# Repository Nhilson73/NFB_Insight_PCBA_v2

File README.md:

# NFB Insight PCBA v2

PCBA **shield/carrier** para **Nebula Fermentation Insight®**, diseñada alrededor del factor de forma inmutable del **Arduino UNO Q**. El repositorio `Nhilson73/nebula_qshield_pcb` es únicamente donante de ingeniería/trazabilidad; no gobierna placement, routing ni topología de producción V2.

## Fuente primaria UNO Q

Toda decisión dependiente del Arduino UNO Q se contrasta primero contra repositorios oficiales Arduino en GitHub (`github.com/Arduino`, especialmente `arduino/docs-content`), luego `docs.arduino.cc` y finalmente datasheets oficiales. La jerarquía y snapshots revisados viven en `docs/SOURCE_OF_TRUTH.md`.

## Frontera del producto / compliance

NFB Insight PCBA v2 es un **shield/carrier del UNO Q**, no un rediseño de su radio. No añade transmisores, antena, matching ni amplificación RF. El **EU Compliance Design Gate** vive en `docs/EU_COMPLIANCE_GATE.md` / `compliance/eu_compliance_contract.json` y cubre EMC, RoHS 3, REACH, WEEE, RED/CE del producto integrado.

## Mecánica y placement — PR #16 / #17 / ECO PR #22 / #24

- UNO Q rotado; origen global `(0,0)`; USB-C hacia `-Y`.
- Envolvente UNO Q / Z0: `53.34 × 68.58 mm`.
- Altura total PCB fija `68.58 mm`; crecimiento solo `+X`.
- `Y=0` = FIELD I/O EDGE; cables hacia `-Y`.
- Gradiente: Z0 UNO Q → Z1 sensores → Z2 digital → Z3 potencia → Z4 actuadores.
- **Ancho final de placement: `242.34 mm`.**
- Z0 `0.00→53.34 mm`.
- Z1 `53.34→108.84 mm` = `55.50 mm`.
- Z2 `108.84→163.34 mm` = `54.50 mm`.
- Z3 `163.34→198.34 mm` = `35.00 mm`.
- Z4 `198.34→242.34 mm` = `44.00 mm`.
- 119 footprints de producción + `J_UNOQ` = 120 footprints.
- 60 nets materializadas desde PR19D; `5V_HMI` es la net ECO añadida después de PR19C.
- PR17 cerró courtyard overlaps y fallos físicos de placement.
- PR22 aplicó el ECO acotado de placement alrededor del `TPSM33625` en Z3.
- PR24 acercó `TP_LOAD_A_POS/NEG` al HX711 en Z2 sin alterar el resto del placement.

## Z1 sensores

- pH/A0 y DO/A5: 0–3 V acondicionados, ESD + `1 kΩ / 100 nF`.
- ORP/A1: divisor `10 kΩ / 20 kΩ`, máximo 3.0 V.
- TEMP/A2-D16: DS18B20 `TEMP_1WIRE`.
- CO₂: Honeywell `MPRLS0030PA00002A`, I²C `0x28`; `CO2_ADC` retirado.
- A4/pad13 = `PUMP_CURRENT_ADC`.

## Z2 digital / bajo ruido

- I²C: MPR `0x28` + DFR1103 `0x66`.
- HX711 3.3 V / 10 SPS en D2/D3.
- HMI: **Nextion Intelligent `NX8048P050-011C-Y`**, 5.0 in capacitiva con enclosure, 800×480; D0/D1 mediante `TXU0202DCUR`.
- Accesorios HMI seleccionados: `SDExtender` + `Nextion BOX Speaker`; `Foca Max` queda como herramienta de programación/servicio.
- HMI+speaker reserva **5 V / 1.5 A**. PR19D cerró el ECO con `5V_HMI` dedicado externo (RECOM `R-78K5.0-2.0L` + fusible 2 A); display/audio ya no cargan `5V_RAIL`.
- Watchdog `TPS3823-30DBVR`, WDI=D4.
- `J_LOADCELL`: Phoenix Contact **1757268 / MSTBA 2,5/4-G-5,08**.

## Z3 potencia

Fuentes: `hardware/power_architecture_contract.json`, `hardware/power_production_netlist.json`, `hardware/power_netclasses.json` y `bom/insight_power_production_bom.csv`.

- 12 V protegido → VIN del UNO Q.
- `5V_RAIL` y `3V3_RAIL` son locales del shield; no se unen a J_UNOQ.5/J_UNOQ.4.
- Protección `SMBJ15A-TR + TPS259470ARPWR`.
- Split `12V_HOST_VIN / 12V_LOGIC / 12V_ACT`.
- `F_ACT=045401.5MR`.
- 5 V `TPSM33625RDNR`; 3.3 V `TLV75533PDBVR`.
- Potencia del chiller externa.

## Z4 actuadores

- Bomba `DRV8242HQRHLRQ1`, D5/D6, IPROPI → A4.
- Solenoide `TPS1HC120CQDYCRQ1`, D7, ILIM ~0.5 A.
- Chiller `AQY212EHAX` + `2N7002`, **dry contact SELV ≤48 V / NO MAINS**.
- D10=`ACT_FAULT_N`; D9 DNP/Reserva.

## Hierarchy EDA — PR #14 / #15

`kicad/NFB_Insight_PCBA_v2.kicad_sch` es el root Z0–Z4. PR #15 materializó las hojas desde JSON/BOM de forma determinista y eliminó completamente la deuda ERC del PR #14.

KiCad **10.0.5** sobre el hierarchy completo:

- **0 Errors**
- **0 Warnings**
- **0 violations**

Los JSON/BOM siguen siendo autoridad; las hojas generadas no deben editarse manualmente para alterar conectividad.

## Routing readiness — PR #18

Fuente: `hardware/routing_contract.json`; narrativa: `docs/FASE5_PR18_ROUTING_READINESS.md`.

PR #18 **no añadió cobre**. Su función fue congelar las reglas antes de rutear:

- exactamente **59/59 nets** cubiertas una sola vez por 11 clases;
- mínimos de potencia heredados de PR #10 no pueden debilitarse;
- `In1.Cu` = **GND continuo; signal routing prohibido**;
- `In2.Cu` = distribución de potencia, sin analógica sensible;
- pH/ORP/DO, load-cell/HX711 y `PUMP_CURRENT_ADC` forman dominio sensible;
- `12V_ACT`, `PUMP_OUT1/2` y `CO2_SOL_POS` forman dominio dirty;
- separación contractual sensitive↔dirty ≥ `1.00 mm` en recorridos paralelos;
- `12V_ACT` y retornos high-current no atraviesan Z1/Z2;
- contactos de chiller permanecen aislados, SELV ≤48 V y sin tie a GND;
- `SW`, `CO2_ADC`, `TEMP_ADC`, `HUM_ADC`, `CO2_PWM`, `CO2_FLOW_PWM` y `RS485_IRQ_RSVD` están prohibidas como nets de producción.

El `TPSM33625` es un módulo integrado y no expone una net SW externa. Su entrada/salida/feedback deben permanecer compactos en Z3.

## Tooling KiCad — PR #25

Las reglas operativas para agentes y automatización KiCad viven en `docs/KICAD_TOOLING_NOTES.md`, `docs/ROUTING_KNOWLEDGE_BASE.md` y `hardware/kicad_tooling_contract.json`.

Principios relevantes:

- `.kicad_pcb + .kicad_pro + .kicad_dru` se tratan como triplete canónico;
- KiCad 10.0.5 DRC es la autoridad física final;
- no se relajan clearances globales para hacer pasar routing;
- pads compuestos se modelan como geometría múltiple pero un endpoint lógico por `(ref,pin)`;
- placement se valida semánticamente, no por identidad textual/UUID del PCB;
- workflows finales de aceptación son `contents: read`.

## Routing incremental — divide y vencerás

El PR #19 monolítico fue usado como **laboratorio de routing** y se cerró sin merge. Demostró que mezclar señales locales, long-haul, potencia y GND en un solo PR aumenta la congestión y dificulta auditar la calidad geométrica.

La base de conocimiento vive en `docs/ROUTING_KNOWLEDGE_BASE.md` y la partición machine-readable en `hardware/routing_batches_contract.json`.

Las **60 nets vigentes** quedan divididas exhaustivamente y sin solapes. Los lotes PR19A/B/C conservan sus manifests históricos; PR19D introduce únicamente la net creada por el ECO HMI:

- **PR19A: 28** nets locales.
- **PR19B: 4** nets analógicas inter-zona: `PH_ADC`, `ORP_ADC`, `DO_ADC`, `PUMP_CURRENT_ADC`.
- **PR19C: 16** nets digital/control inter-zona.
- **PR19D: 1** net ECO local de potencia HMI: `5V_HMI`.
- **PR20A: 10** nets de potencia + salidas de actuadores.
- **PR20B: 1** net GND, tratada como plano `In1.Cu` + stitching; el probe experimental identificó 83 endpoints.

Total vigente: **28 + 4 + 16 + 1 + 10 + 1 = 60**.

Política de merge: **ALL_OR_NOTHING por lote**. No se mergea progreso parcial de un lote: todas sus nets deben estar conectadas, ninguna net futura puede ser tocada, no puede haber shorts/clearance/courtyard nuevos y placement/outline deben permanecer congelados.

La calidad de routing se evalúa también por longitud, segmentos, vías y cambios de dirección. Una ruta meandriforme no se acepta únicamente porque pase conectividad.

## PR19A — 28 nets locales / PR #28

El primer lote físico de producción queda materializado y persistido sobre el placement post-PR22/post-PR24.

Estado congelado del checkpoint:

- **28/28 nets PR19A con cobre.**
- **31/31 nets de lotes futuros sin cobre.**
- **523 segmentos.**
- **24 vías.**
- `In1.Cu`: **0 signal tracks**.
- copper zones: **0**.
- KiCad 10.0.5 DRC: **0 errors**.
- DRC warnings conocidos: **255**, exclusivamente deuda de serigrafía/texto:
  - `silk_edge_clearance`: 13;
  - `text_height`: 1;
  - `silk_overlap`: 173;
  - `silk_over_copper`: 68.
- unconnected restantes: **204**; ninguno pertenece a las 28 nets PR19A y corresponden a lotes futuros todavía no rutados.

La pasada de calidad redujo dos rutas excesivamente fragmentadas sin cambiar sus corredores DRC-clean:

- `5V_PGOOD`: **143 → 12 segmentos**.
- `WDT_MR_N`: **100 → 10 segmentos**.

El PCB de este checkpoint está persistido en `kicad/NFB_Insight_PCBA_v2.kicad_pcb`; el manifest de evidencia vive en `hardware/pr19a_local_routing_manifest.json` y el probe en `hardware/pr19a_local_probe.json`.

## PR19B — 4 nets analógicas long-haul / PR #30

PR #30 materializó el segundo lote de producción bajo política **ALL_OR_NOTHING**:

- `PH_ADC`
- `ORP_ADC`
- `DO_ADC`
- `PUMP_CURRENT_ADC`

Checkpoint congelado post-merge:

- **4/4 nets PR19B conectadas.**
- PR19A preservado íntegramente: **523 segmentos / 24 vías**.
- PR19B añadió **32 segmentos / 7 vías**.
- acumulado de producción: **555 segmentos / 31 vías**.
- **27 nets futuras sin cobre** al cierre de PR19B.
- `In1.Cu`: **0 signal tracks**.
- copper zones: **0**.
- KiCad 10.0.5 DRC: **0 errors**.
- warnings conocidos: **255**, sin deuda nueva de cobre.
- unconnected restantes: **192**.
- placement y outline congelados sin cambios.
- workflows finales de aceptación: **15/15 verdes**.

Los guardrails históricos fueron promovidos para reconocer de forma exacta `PRE_ROUTING → PR19A → PR19B` mediante contratos/manifests versionados, sin relajar DRC. Evidencia: `hardware/pr19b_analog_routing_manifest.json`; narrativa: `docs/FASE5_PR19B_ANALOG_ROUTING.md`.

## PR19C — 16 nets digital/control inter-zona / PR #31

PR #31 materializó el tercer lote de producción bajo política **ALL_OR_NOTHING**:

`ACT_FAULT_N`, `CHILLER_CTL`, `CO2_SOL_CTL`, `HMI_RX`, `HMI_TX`, `HX711_DOUT`, `HX711_SCK`, `I2C_SCL`, `I2C_SDA`, `LED_STATUS`, `MCU_NRST`, `MCU_WDI`, `PUMP_DIR`, `PUMP_PWM`, `TEMP_1WIRE`, `UNO_IOREF_3V3`.

Checkpoint congelado post-merge:

- **16/16 nets PR19C conectadas.**
- PR19A y PR19B preservados: **32/32 nets previas**.
- PR19C añadió **362 segmentos / 88 vías**.
- acumulado de producción: **917 segmentos / 119 vías**.
- **48/59 nets de producción ya ruteadas**.
- **11 nets PR20A/PR20B permanecen sin cobre**.
- `In1.Cu`: **0 signal tracks**.
- copper zones: **0**.
- KiCad 10.0.5 DRC: **0 errors**.
- warnings conocidos: **255**, exactamente la deuda histórica de serigrafía/texto.
- unconnected restantes: **154**.
- placement y outline congelados sin cambios.
- todas las nets PR19C cumplen el gate geométrico de **≤10 vías por net**.
- workflows finales de aceptación: **15/15 verdes**.

Durante el cierre se aplicaron dos correcciones geométricas controladas sin alterar conectividad ni reglas: `CO2_ILIM` se reperfiló **4→4 segmentos / 0→0 vías** para abrir el corredor de `ACT_FAULT_N`, y una vía `I2C_SDA` se desplazó localmente para cerrar el spacing `hole_to_hole` sin cambiar topología ni conteos.

Los guardrails históricos reconocen ahora de forma exacta `PRE_ROUTING → PR19A → PR19B → PR19C`. El manifest final es `hardware/pr19c_digital_routing_manifest.json` con status `DIGITAL_ROUTING_PR19C`; la narrativa vive en `docs/FASE5_PR19C_DIGITAL_ROUTING.md`.

## RF / enclosure

La fuente primaria Arduino revisada no publicó un antenna keepout numérico textual. NFB no inventa una distancia. Z0 permanece libre de footprints NFB y, durante routing, solo se permiten escapes mínimos hacia/desde `J_UNOQ`; la revisión final de cobre/enclosure/stacking/RF sigue siendo un gate de release.

## Estado actual

Placement y ECOs PR22/PR24 están congelados. PR18 congeló las reglas de routing y PR25 consolidó tooling KiCad. **PR28 cerró PR19A (28/28), PR30 cerró PR19B (4/4), PR31 cerró PR19C (16/16) y PR19D cerró el ECO HMI `5V_HMI` 1/1. El PCB vigente queda en 49/60 nets ruteadas, 924 segmentos, 121 vías, 0 zones, DRC físico 0 errores y 151 unconnected. PR20A conserva sus 10 nets históricas y queda como siguiente lote de cobre.**

**Siguiente checkpoint de producción: PR20A — routing de 10 nets de potencia + salidas de actuadores (`12V_IN_RAW`, `12V_PROTECTED`, `12V_HOST_VIN`, `12V_LOGIC`, `12V_ACT`, `5V_RAIL`, `3V3_RAIL`, `PUMP_OUT1`, `PUMP_OUT2`, `CO2_SOL_POS`). PR20B/GND permanece diferido hasta cerrar PR20A.**

## HMI power ECO — PR19D

La HMI Nextion `NX8048P050-011C-Y` + BOX Speaker usa alimentación externa dedicada `5V_HMI`: Littelfuse `0FHM0001ZXJ` + `0997002.WXN` 2 A → RECOM `R-78K5.0-2.0L` 5 V/2 A. La corriente de display/audio no atraviesa `5V_RAIL` de la PCBA. En la placa, `5V_HMI` solo alimenta `J_HMI.1`, `TXU0202 VCCB` y `C_HMI_B`. Nuevo lote de routing `PR19D` 1/1 antes de PR20A. Ver `docs/HMI_POWER_ECO_PR19D.md`.

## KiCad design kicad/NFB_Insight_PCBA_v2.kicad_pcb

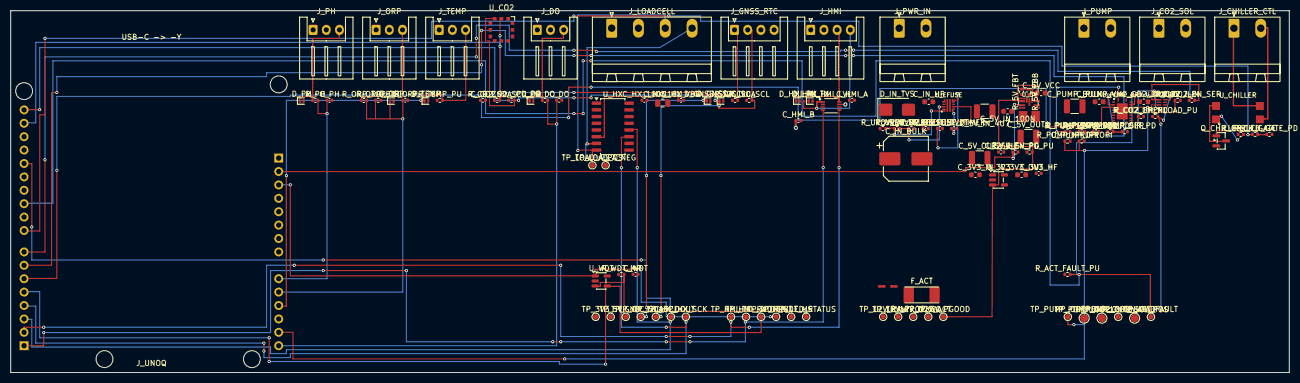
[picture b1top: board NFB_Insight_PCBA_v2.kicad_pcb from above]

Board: 4 copper layers, 242.3 x 68.6 mm, 120 parts (0 on the bottom side), 60 nets.

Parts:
C_3V3_HF, C_5V_HF: 100nF 25V X7R; C_0402_1005Metric
C_3V3_IN, C_3V3_OUT, C_5V_VCC: 1uF 25V X7R; C_0603_1608Metric
C_5V_IN_4U7: 4.7uF 50V X7R; C_1210_3225Metric
C_5V_IN_100N: 100nF 50V X7R; C_0603_1608Metric
C_5V_OUT1, C_5V_OUT2: 22uF 16V X7R; C_1210_3225Metric
C_CO2: 100nF 25V X7R; C_0402_1005Metric
C_CO2_DRV: 100nF 50V X7R; C_0603_1608Metric
C_DO: 100nF 25V X7R; C_0402_1005Metric
C_EFUSE_DVDT: 3.3nF 50V X7R; C_0402_1005Metric
C_EFUSE_ITIMER: 2.2nF 50V X7R; C_0402_1005Metric
C_HMI_A: 100nF 25V X7R; C_0402_1005Metric
C_HMI_B: 100nF 25V X7R; C_0402_1005Metric
C_HX_10U: 10uF 10V X5R; C_0805_2012Metric
C_HX_100N: 100nF 25V X7R; C_0402_1005Metric
C_HX_VBG: 100nF 25V X7R; C_0402_1005Metric
C_IN_BULK: 100uF 25V; CP_Elec_8x6.2
C_IN_HF: 100nF 50V X7R; C_0603_1608Metric
C_ORP: 100nF 25V X7R; C_0402_1005Metric
C_PH: 100nF 25V X7R; C_0402_1005Metric
C_PUMP_BULK: 22uF 25V X7R; C_1210_3225Metric
C_PUMP_IPROPI: 100nF; C_0402_1005Metric
C_PUMP_VM: 100nF 50V X7R; C_0603_1608Metric
C_WDT: 100nF 25V X7R; C_0402_1005Metric
D_DO: PESD3V3U1UL; D_SOD-882
D_GNSS_SCL: PESD3V3U1UL; D_SOD-882
D_GNSS_SDA: PESD3V3U1UL; D_SOD-882
D_HMI_RX: PESD5V0U1UL; D_SOD-882
D_HMI_TX: PESD5V0U1UL; D_SOD-882
D_IN_TVS: SMBJ15A 600W 15V uni; D_SMB
D_ORP: PESD3V3U1UL; D_SOD-882
D_PH: PESD3V3U1UL; D_SOD-882
D_TEMP: PESD3V3U1UL; D_SOD-882
F_ACT: 1.5A 125V Slo-Blo Nano2; Littelfuse_0454_NANO2
J_CHILLER_CTL: MSTBA 2,5/2-G-5.08; PhoenixContact_MSTBA_2,5_2-G-5,08_1x02_P5.08mm_Horizontal
J_CO2_SOL: MSTBA 2,5/2-G-5,08; PhoenixContact_MSTBA_2,5_2-G-5,08_1x02_P5.08mm_Horizontal
J_DO: JST XH 3p side-entry; JST_XH_S3B-XH-A_1x03_P2.50mm_Horizontal
J_GNSS_RTC: JST XH 4p side-entry; JST_XH_S4B-XH-A_1x04_P2.50mm_Horizontal
J_HMI: JST XH 4p side-entry; JST_XH_S4B-XH-A_1x04_P2.50mm_Horizontal
J_LOADCELL: MSTBA 2,5/4-G-5,08; PhoenixContact_MSTBA_2,5_4-G-5,08_1x04_P5.08mm_Horizontal
J_ORP: JST XH 3p side-entry; JST_XH_S3B-XH-A_1x03_P2.50mm_Horizontal
J_PH: JST XH 3p side-entry; JST_XH_S3B-XH-A_1x03_P2.50mm_Horizontal
J_PUMP: MSTBA 2,5/2-G-5,08; PhoenixContact_MSTBA_2,5_2-G-5,08_1x02_P5.08mm_Horizontal
J_PWR_IN: MSTBA 2,5/2-G-5,08; PhoenixContact_MSTBA_2,5_2-G-5,08_1x02_P5.08mm_Horizontal
J_TEMP: JST XH 3p side-entry; JST_XH_S3B-XH-A_1x03_P2.50mm_Horizontal
J_UNOQ: Arduino_UNO_Q_Carrier_Rotated
NT_HOST: NET_TIE_2; NetTie-2_SMD_Pad0.5mm
NT_LOGIC: NET_TIE_2; NetTie-2_SMD_Pad0.5mm
Q_CHILLER: 2N7002; SOT-23
R_5V_EN_PD: 100k 1%; R_0402_1005Metric
R_5V_FBB: 10k 1%; R_0402_1005Metric
R_5V_FBT: 40.2k 1%; R_0402_1005Metric
R_5V_PG_PU: 47k 1%; R_0402_1005Metric
R_ACT_FAULT_PU: 10k; R_0402_1005Metric
R_CH_GATE: 1k; R_0402_1005Metric
R_CH_GATE_PD: 100k; R_0402_1005Metric
R_CH_LED: 360R 1%; R_0402_1005Metric
R_CO2_EN_PD: 100k; R_0402_1005Metric
R_CO2_EN_SER: 100R; R_0402_1005Metric
R_CO2_ILIM: 27k 1%; R_0402_1005Metric
R_CO2_OPENLOAD_PU, R_CO2_SCL_PU, R_CO2_SDA_PU: 10k; R_0402_1005Metric
R_DO: 1k 1%; R_0402_1005Metric
R_EFUSE_ILIM: 750R 1%; R_0402_1005Metric
R_I2C_SCL, R_I2C_SDA: 4.7k 1%; R_0402_1005Metric
R_ORP_BOT: 20k 0.1%; R_0402_1005Metric
R_ORP_TOP: 10k 0.1%; R_0402_1005Metric
R_PH: 1k 1%; R_0402_1005Metric
R_PUMP_DIR_PD: 100k; R_0402_1005Metric
R_PUMP_DIR_SER: 100R; R_0402_1005Metric
R_PUMP_IPROPI: 1.5k 1%; R_0402_1005Metric
R_PUMP_PWM_PD: 100k; R_0402_1005Metric
R_PUMP_PWM_SER: 100R; R_0402_1005Metric
R_PUMP_SR: 22k; R_0402_1005Metric
R_TEMP_PU: 4.7k 1%; R_0402_1005Metric
R_UVOV_R1: 470k 1%; R_0402_1005Metric
R_UVOV_R2: 11k 1%; R_0402_1005Metric
R_UVOV_R3: 47k 1%; R_0402_1005Metric
R_WDT_MR: 10k 1%; R_0402_1005Metric
TP_3V3, TP_5V, TP_5V_PGOOD, TP_12V_ACT, TP_12V_LOGIC, TP_12V_PROT, TP_12V_RAW: PCB test point; TestPoint_Pad_D1.0mm
TP_ACT_FAULT: TESTPOINT; TestPoint_Pad_D1.0mm
TP_CO2_OPENLOAD: TESTPOINT; TestPoint_Pad_D1.0mm
TP_CO2_SOL_POS: TESTPOINT; TestPoint_Pad_D1.5mm
TP_GND: PCB test point; TestPoint_Pad_D1.0mm
TP_HMI_RX: PCB test point; TestPoint_Pad_D1.0mm
TP_HMI_TX: PCB test point; TestPoint_Pad_D1.0mm
TP_HX_DOUT: PCB test point; TestPoint_Pad_D1.0mm
TP_HX_SCK: PCB test point; TestPoint_Pad_D1.0mm
TP_I2C_SCL, TP_I2C_SDA: PCB test point; TestPoint_Pad_D1.0mm
TP_LED_STATUS: PCB test point; TestPoint_Pad_D1.0mm
TP_LOAD_A_NEG: PCB test point; TestPoint_Pad_D1.0mm
TP_LOAD_A_POS: PCB test point; TestPoint_Pad_D1.0mm
TP_NRST: PCB test point; TestPoint_Pad_D1.0mm
TP_PUMP_CURRENT: TESTPOINT; TestPoint_Pad_D1.0mm
TP_PUMP_OUT1, TP_PUMP_OUT2: TESTPOINT; TestPoint_Pad_D1.5mm
TP_WDI: PCB test point; TestPoint_Pad_D1.0mm
TP_WDT_MR: PCB test point; TestPoint_Pad_D1.0mm
U_3V3: TLV75533 3.3V/500mA; SOT-23-5
U_5V: TPSM33625 5V/2.5A; TI_RDN0011A_TPSM33625
U_CHILLER: PhotoMOS GE DIP4 1 Form A; Panasonic_AQY212EHAX_DIP4_SMD
U_CO2: MPR 0-30 psi abs I2C 0x28; Honeywell_MPR_LongPort_12Pad
U_CO2_DRV: TPS1HC120C-Q1; TI_DYC0008A_TPS1HC120
U_EFUSE: TPS259470A; TI_RPW0010A_TPS259470A
U_HMI_LVL: TXU0202; TI_DCU0008A_TXU0202
U_HX: HX711 24-bit; SOP-16_4.4x10.4mm_P1.27mm
U_PUMP_DRV: DRV8242H-Q1; TI_RHL0020B_DRV8242
U_WDT: TPS3823-30 1.6s; SOT-23-5

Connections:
3V3_RAIL: C_3V3_HF.1, C_3V3_OUT.1, C_CO2.1, C_HMI_A.1, C_HX_10U.1, C_HX_100N.1, C_WDT.1, J_GNSS_RTC.4, J_LOADCELL.1, J_TEMP.1, R_ACT_FAULT_PU.1, R_CH_LED.1, R_CO2_OPENLOAD_PU.1, R_CO2_SCL_PU.1, R_CO2_SDA_PU.1, R_I2C_SCL.1, R_I2C_SDA.1, R_TEMP_PU.1, R_WDT_MR.1, TP_3V3.1, U_3V3.5, U_CO2.12, U_HMI_LVL.3, U_HMI_LVL.6, U_HX.1, U_HX.3, U_HX.16, U_PUMP_DRV.16, U_WDT.5
5V_FB: R_5V_FBB.1, R_5V_FBT.2, U_5V.9
5V_HMI: C_HMI_B.1, J_HMI.1, U_HMI_LVL.7
5V_PGOOD: R_5V_PG_PU.2, TP_5V_PGOOD.1, U_3V3.3, U_5V.1
5V_RAIL: C_3V3_IN.1, C_5V_HF.1, C_5V_OUT1.1, C_5V_OUT2.1, J_DO.1, J_ORP.1, J_PH.1, R_5V_FBT.1, R_5V_PG_PU.1, TP_5V.1, U_3V3.1, U_5V.4
5V_VCC: C_5V_VCC.1, U_5V.8, U_5V.11
12V_ACT: C_CO2_DRV.1, C_PUMP_BULK.1, C_PUMP_VM.1, F_ACT.2, TP_12V_ACT.1, U_CO2_DRV.8, U_PUMP_DRV.6, U_PUMP_DRV.15
12V_HOST_VIN: J_UNOQ.8, NT_HOST.2
12V_IN_RAW: C_IN_HF.1, D_IN_TVS.1, J_PWR_IN.1, R_UVOV_R1.1, TP_12V_RAW.1, U_EFUSE.5
12V_LOGIC: C_5V_IN_4U7.1, C_5V_IN_100N.1, NT_LOGIC.2, TP_12V_LOGIC.1, U_5V.3
12V_PROTECTED: C_IN_BULK.1, F_ACT.1, NT_HOST.1, NT_LOGIC.1, TP_12V_PROT.1, U_EFUSE.6
ACT_FAULT_N: J_UNOQ.25, R_ACT_FAULT_PU.2, TP_ACT_FAULT.1, U_CO2_DRV.1, U_PUMP_DRV.18
CHILLER_CONTACT_A: J_CHILLER_CTL.1, U_CHILLER.3
CHILLER_CONTACT_B: J_CHILLER_CTL.2, U_CHILLER.4
CHILLER_CTL: J_UNOQ.23, R_CH_GATE.1
CHILLER_GATE: Q_CHILLER.1, R_CH_GATE.2, R_CH_GATE_PD.1
CHILLER_LED_A: R_CH_LED.2, U_CHILLER.1
CHILLER_LED_K: Q_CHILLER.3, U_CHILLER.2
CO2_EN_DRV: R_CO2_EN_PD.1, R_CO2_EN_SER.2, U_CO2_DRV.4
CO2_ILIM: R_CO2_ILIM.1, U_CO2_DRV.2
CO2_OPENLOAD_N: R_CO2_OPENLOAD_PU.2, TP_CO2_OPENLOAD.1, U_CO2_DRV.5
CO2_SOL_CTL: J_UNOQ.22, R_CO2_EN_SER.1
CO2_SOL_POS: J_CO2_SOL.1, TP_CO2_SOL_POS.1, U_CO2_DRV.7
DO_ADC: C_DO.1, J_UNOQ.14, R_DO.2
DO_FIELD_SIG: D_DO.1, J_DO.3, R_DO.1
EFUSE_DVDT: C_EFUSE_DVDT.1, U_EFUSE.7
EFUSE_EN_UVLO: R_UVOV_R1.2, R_UVOV_R2.1, U_EFUSE.1
EFUSE_ILM: R_EFUSE_ILIM.1, U_EFUSE.9
EFUSE_ITIMER: C_EFUSE_ITIMER.1, U_EFUSE.10
EFUSE_OVLO: R_UVOV_R2.2, R_UVOV_R3.1, U_EFUSE.2
GND: C_3V3_HF.2, C_3V3_IN.2, C_3V3_OUT.2, C_5V_HF.2, C_5V_IN_4U7.2, C_5V_IN_100N.2, C_5V_OUT1.2, C_5V_OUT2.2, C_5V_VCC.2, C_CO2.2, C_CO2_DRV.2, C_DO.2, C_EFUSE_DVDT.2, C_EFUSE_ITIMER.2, C_HMI_A.2, C_HMI_B.2, C_HX_10U.2, C_HX_100N.2, C_HX_VBG.2, C_IN_BULK.2, C_IN_HF.2, C_ORP.2, C_PH.2, C_PUMP_BULK.2, C_PUMP_IPROPI.2, C_PUMP_VM.2, C_WDT.2, D_DO.2, D_GNSS_SCL.2, D_GNSS_SDA.2, D_HMI_RX.2, D_HMI_TX.2, D_IN_TVS.2, D_ORP.2, D_PH.2, D_TEMP.2, J_CO2_SOL.2, J_DO.2, J_GNSS_RTC.3, J_HMI.2, J_LOADCELL.2, J_ORP.2, J_PH.2, J_PWR_IN.2, J_TEMP.2, J_UNOQ.6, J_UNOQ.7, J_UNOQ.29, Q_CHILLER.2, R_5V_EN_PD.2, R_5V_FBB.2, R_CH_GATE_PD.2, R_CO2_EN_PD.2, R_CO2_ILIM.2, R_EFUSE_ILIM.2, R_ORP_BOT.2, R_PUMP_DIR_PD.2, R_PUMP_IPROPI.2, R_PUMP_PWM_PD.2, R_PUMP_SR.2, R_UVOV_R3.2, TP_GND.1, U_3V3.2, U_5V.10, U_CO2.10, U_CO2_DRV.3, U_CO2_DRV.6, U_EFUSE.8, U_HMI_LVL.2, U_HX.4, U_HX.5, U_HX.14, U_HX.15, U_PUMP_DRV.2, U_PUMP_DRV.5, U_PUMP_DRV.9, U_PUMP_DRV.10, U_PUMP_DRV.11, U_PUMP_DRV.12, U_PUMP_DRV.19, U_PUMP_DRV.20, U_PUMP_DRV.21, U_WDT.2
HMI_FIELD_RX: D_HMI_RX.1, J_HMI.3, U_HMI_LVL.8
HMI_FIELD_TX: D_HMI_TX.1, J_HMI.4, U_HMI_LVL.1
HMI_RX: J_UNOQ.15, TP_HMI_RX.1, U_HMI_LVL.4
HMI_TX: J_UNOQ.16, TP_HMI_TX.1, U_HMI_LVL.5
HX711_DOUT: J_UNOQ.17, TP_HX_DOUT.1, U_HX.12
HX711_SCK: J_UNOQ.18, TP_HX_SCK.1, U_HX.11
HX_VBG: C_HX_VBG.1, U_HX.6
I2C_SCL: D_GNSS_SCL.1, J_GNSS_RTC.2, J_UNOQ.32, R_CO2_SCL_PU.2, R_I2C_SCL.2, TP_I2C_SCL.1, U_CO2.3
I2C_SDA: D_GNSS_SDA.1, J_GNSS_RTC.1, J_UNOQ.31, R_CO2_SDA_PU.2, R_I2C_SDA.2, TP_I2C_SDA.1, U_CO2.2
LED_STATUS: J_UNOQ.28, TP_LED_STATUS.1
LOAD_A_NEG: J_LOADCELL.4, TP_LOAD_A_NEG.1, U_HX.7
LOAD_A_POS: J_LOADCELL.3, TP_LOAD_A_POS.1, U_HX.8
MCU_NRST: J_UNOQ.3, TP_NRST.1, U_WDT.1
MCU_WDI: J_UNOQ.19, TP_WDI.1, U_WDT.4
ORP_ADC: C_ORP.1, D_ORP.1, J_UNOQ.10, R_ORP_BOT.1, R_ORP_TOP.2
ORP_FIELD_SIG: J_ORP.3, R_ORP_TOP.1
PH_ADC: C_PH.1, J_UNOQ.9, R_PH.2
PH_FIELD_SIG: D_PH.1, J_PH.3, R_PH.1
PUMP_CURRENT_ADC: C_PUMP_IPROPI.1, J_UNOQ.13, R_PUMP_IPROPI.1, TP_PUMP_CURRENT.1, U_PUMP_DRV.17
PUMP_DIR: J_UNOQ.21, R_PUMP_DIR_SER.1
PUMP_DIR_DRV: R_PUMP_DIR_PD.1, R_PUMP_DIR_SER.2, U_PUMP_DRV.3
PUMP_OUT1: J_PUMP.1, TP_PUMP_OUT1.1, U_PUMP_DRV.7, U_PUMP_DRV.8
PUMP_OUT2: J_PUMP.2, TP_PUMP_OUT2.1, U_PUMP_DRV.13, U_PUMP_DRV.14
PUMP_PWM: J_UNOQ.20, R_PUMP_PWM_SER.1
PUMP_PWM_DRV: R_PUMP_PWM_PD.1, R_PUMP_PWM_SER.2, U_PUMP_DRV.4
PUMP_SR_CFG: R_PUMP_SR.1, U_PUMP_DRV.1
TEMP_1WIRE: D_TEMP.1, J_TEMP.3, J_UNOQ.11, R_TEMP_PU.2
UNO_IOREF_3V3: J_UNOQ.2, R_5V_EN_PD.1, U_5V.2
WDT_MR_N: R_WDT_MR.2, TP_WDT_MR.1, U_WDT.3

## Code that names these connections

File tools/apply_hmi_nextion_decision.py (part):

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        "routing_frozen": True,
        "footprint_change_on_pcba": False,
        "reason": "PR19C ya cerró HMI_RX/HMI_TX; ITEAD publica XH2.54 4P pero no un MPN JST exacto. Se conserva la geometría de J_HMI y se exige prueba de apareamiento del arnés en first article antes de release.",
        "pinout_board": {"1": "5V_RAIL", "2": "GND", "3": "HMI_FIELD_RX", "4": "HMI_FIELD_TX"},
        "signal_mapping": {
            "NFB_HMI_FIELD_RX": "Nextion TX",
            "NFB_HMI_FIELD_TX": "Nextion RX",
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3. el arnés final debe pasar **mating test de first article** antes de release;
4. cualquier cambio posterior de `J_HMI` será un ECO de footprint/routing explícito.

Mapping lógico: `HMI_TX` del UNO → TXU0202 → `HMI_FIELD_RX` → RX de Nextion; TX de Nextion → `HMI_FIELD_TX` → TXU0202 → `HMI_RX` del UNO. Campo protegido con `PESD5V0U1UL,315`.

## Accesorios seleccionados

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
